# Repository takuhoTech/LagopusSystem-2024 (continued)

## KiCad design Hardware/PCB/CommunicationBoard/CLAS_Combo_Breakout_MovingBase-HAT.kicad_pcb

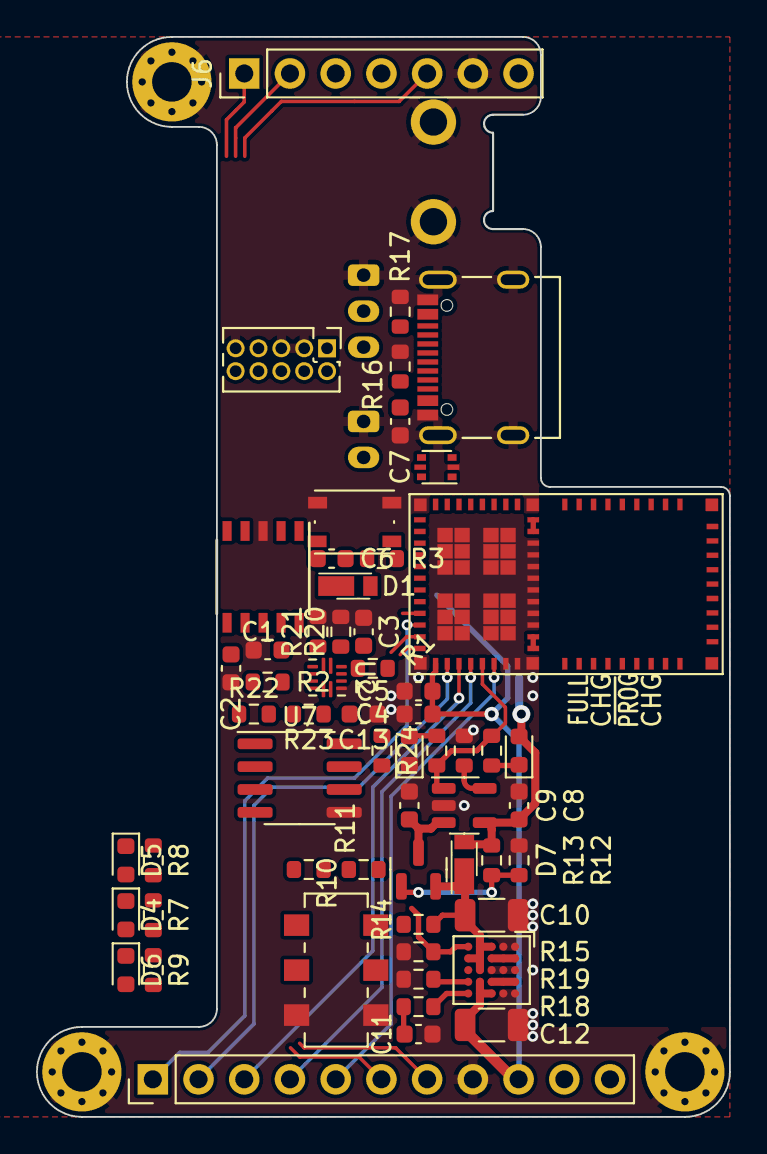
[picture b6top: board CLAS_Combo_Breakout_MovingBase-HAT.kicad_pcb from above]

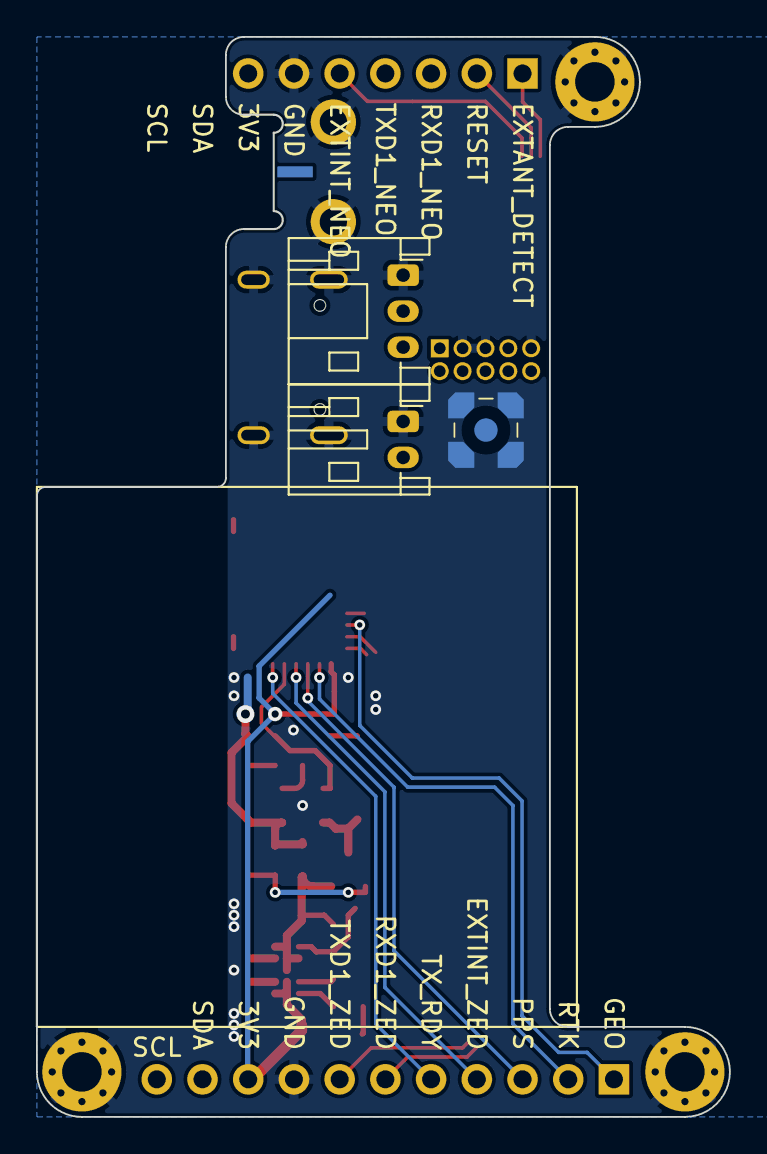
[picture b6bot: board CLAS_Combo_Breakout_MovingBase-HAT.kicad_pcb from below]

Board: 4 copper layers, 38.5 x 60.0 mm, 65 parts (4 on the bottom side), 57 nets.

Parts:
C1, C2, C3, C5, C6, C8, C13: 0.1u; C_0603_1608Metric
C4: 1u; C_0603_1608Metric
C7, C9: 47μF6.3V X5R 1608; C_0603_1608Metric
C10: 100μF10V X5R 3216; C_1206_3216Metric
C11: 2200pF50V CH 1608; C_0603_1608Metric
C12: 220μF4V X6S 3216; C_1206_3216Metric
D1, D7: CUHS20S30
D2: RED; LED_0603_1608Metric
D3: GREEN; LED_0603_1608Metric
D4: RTK; LED_0603_1608Metric
D5: GEO; LED_0603_1608Metric
D6: PPS; LED_0603_1608Metric
H1, H2, H3: MH; MountingHole_2.2mm_M2_Pad_Via
J1: MMCX; MMCX_Samtec_MMCX-P-P-H-ST-SM1_Male
J2: SMA; SMA_Molex_0732512440_embed
J3: SWD; PinHeader_2x05_P1.27mm_Vertical
J4: ZED; PinHeader_1x11_P2.54mm_Vertical
J5: BATT; JST_PH_S2B-PH-K_1x02_P2.00mm_Horizontal
J6: NEO; PinHeader_1x07_P2.54mm_Vertical
J7: USB_C_Receptacle_USB2.0; USB_C_Receptacle_5077CR-16-SMC2-BK-TR
J8: RS485; JST_PH_S3B-PH-K_1x03_P2.00mm_Horizontal
Q1: AO3415A; SOT-23
R1, R2: 33; R_0603_1608Metric
R3, R18, R20, R21, R22, R23: 10k; R_0603_1608Metric
R4: RILIM; R_0603_1608Metric
R5, R6, R7, R8, R9: 1k; R_0603_1608Metric
R10: 1M; R_0603_1608Metric
R11: 510k; R_0603_1608Metric
R12: 100k; R_0603_1608Metric
R13: 10; R_0603_1608Metric
R14: Rtop; R_0603_1608Metric
R15: Rbtm; R_0603_1608Metric
R16, R17: 5.1k; R_0603_1608Metric
R19: 26.2k; R_0603_1608Metric
R24: 120; R_0603_1608Metric
SW1: SW_Push; SW_Push_1P1T_NO_Vertical_Wuerth_434133025816
SW2: SW_SPDT; SW_SPDT_SSSS213202
U1: CH340K; SSOP-10_3.9x4.9mm_P1.00mm
U2: TMUX131; Texas_RMG0012A_1.8x1.8mm_P0.4mm
U3: ISP4520-AS; ISP4520-AS_with_Keep-Out
U4: MCP73831-2-OT; SOT-23-5
U5: LTM4693; Converter_DCDC_AnalogDevices_LTM4693
U6: USBLC6-2P6; SOT-666
U7: MAX3485; SOIC-8_3.9x4.9mm_P1.27mm

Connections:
+3.3V: C1.1, C2.1, C3.2, C4.1, C5.1, C12.1, C13.2, D1.1 (K), J3.1 (VTref), J4.9, J6.7, R3.1, R7.1, R22.1, R23.1, U1.7 (VCC), U1.10 (V3), U2.12 (VDD), U3.15 (VDD), U5.C5 (VOUT), U5.D4 (VOUT), U5.D5 (VOUT), U7.8 (VCC)
+BATT: C9.1, J5.2, Q1.3 (D), R10.1, U4.3 (VBAT)
/BaseMode: R21.1, U2.2 (SEL1), U3.9 (P0_13), U7.2 (~RE), U7.3 (DE)
/CH340K_RXD: U1.9 (RXD), U2.3 (S1B)
/CH340K_TXD: R2.2, U2.4 (S2B)
/D+: J7.A6 (D+), J7.B6 (D+), U1.1 (UD+), U6.1 (I/O1), U6.6 (I/O1)
/D-: J7.A7 (D-), J7.B7 (D-), U1.2 (UD-), U6.3 (I/O2), U6.4 (I/O2)
/DTR: C6.1, U1.4 (~DTR)
/EXTANT_DETECT: J6.1, U3.6 (P0_22)
/EXTINT_NEO: J6.5, U3.3 (P0_10/NFC2)
/EXTINT_ZED: J4.4, U3.18 (P0_30_AIN6)
/GEO: J4.1, R8.1, U3.11 (P0_05_AIN3)
/RESET: C6.2, D1.2 (A), J3.10 (~RESET), R3.2, SW1.1, U3.40 (P0_21/RESET)
/RESET_ZED_NEO: J6.2, U3.4 (P0_17)
/RS485_A: J8.3, R24.2, U7.6 (A)
/RS485_B: J8.2, R24.1, U7.7 (B)
/RS485_RXD: R23.2, U2.7 (S1A), U7.4 (DI)
/RS485_TXD: R22.2, U2.6 (S2C), U7.1 (RO)
/RTK: D4.1 (K), J4.2, U3.16 (P0_02_AIN0)
/RXD1_ZED: J4.6, U2.5 (S1C)
/RoverMode: R20.1, U2.1 (SEL0), U3.7 (P0_09/NFC1)
/SCL: J4.11, U3.5 (P0_07)
/SDA: J4.10, U3.2 (P0_12)
/SWDCLK: J3.4 (SWDCLK/TCK), U3.37 (SWDCLK)
/SWDIO: J3.2 (SWDIO/TMS), U3.38 (SWDIO)
/TP: J4.3, R9.1, U3.17 (P0_31_AIN7)
/TXD1_ZED: J4.7, U2.8 (S2A)
/TX_RDY: J4.5, U3.20 (P0_28_AIN4)
/VBAT: R10.2, R11.1, U3.13 (P0_03_AIN1)
/nRF52_RXD: U2.10 (D2), U3.8 (P0_08)
/nRF52_TXD: R1.1, U2.11 (D1)
/~CHG_STAT: R5.2, R6.1, U3.19 (P0_29_AIN5), U4.1 (STAT)
/~VBAT_EN: R11.2, U3.12 (P0_04_AIN2)
GND: C1.2, C2.2, C3.1, C4.2, C5.2, C7.1, C8.1, C9.2, C10.2, C11.2, C12.2, C13.1, D3.1 (K), D5.1 (K), D6.1 (K), H1.1, H2.1, H3.1, J1.2 (Ext), J2.2 (Ext), J3.3 (GND), J3.5 (GND), J3.9 (GNDDetect), J4.8, J5.1, J6.6, J7.A1 (GND), J7.A12 (GND), J7.B1 (GND), J7.B12 (GND), J7.S1 (SHIELD), J8.1, R4.1, R12.1, R15.2, R16.2, R17.2, R19.2, R20.2, R21.2, SW1.2, SW2.3 (C), U1.3 (GND), U2.9 (GND), U3.1 (GND), U3.14 (GND), U3.21 (GND), U3.22 (GND), U3.23 (GND), U3.26 (GND), U3.27 (GND), U3.28 (GND), U3.29 (GND), U3.30 (GND), U3.31 (GND), U3.32 (GND), U3.33 (GND), U3.36 (GND), U3.74 (GND), U4.2 (VSS), U5.A1 (GND), U5.A3 (GND), U5.A5 (GND), U5.B1 (GND), U5.B3 (GND), U5.B5 (GND), U5.C3 (GND), U6.2 (GND), U7.5 (GND)
unnamed: C11.1, R18.2
unnamed: D2.1 (K), R5.1
unnamed: D3.2 (A), R6.2
unnamed: D4.2 (A), R7.2
unnamed: D5.2 (A), R8.2
unnamed: D6.2 (A), R9.2
unnamed: J1.1 (In), J2.1 (In)
unnamed: J7.A5 (CC1), R16.1
unnamed: J7.B5 (CC2), R17.1
unnamed: Q1.1 (G), R12.2, R13.2
unnamed: R1.2, U3.10 (P0_06)
unnamed: R2.1, U1.8 (TXD)
unnamed: R4.2, U4.5 (PROG)
unnamed: R14.2, SW2.1 (A)
unnamed: R15.1, SW2.2 (B), U5.E1 (RUN/UVLO)
unnamed: R18.1, U5.E5 (COMP)
unnamed: R19.1, U5.E4 (FB)
unnamed: U3.24 (LORA_TR), U3.25 (LORA_ANT)
unnamed: U3.34 (BLE_ANT), U3.35 (BLE_TR)
unnamed: U5.A2 (SW1), U5.B2 (SW1), U5.C2 (SW1)
unnamed: U5.A4 (SW2), U5.B4 (SW2), U5.C4 (SW2)
VBUS: C7.2, C8.2, D2.2 (A), D7.2 (A), J7.A4 (VBUS), J7.A9 (VBUS), J7.B4 (VBUS), J7.B9 (VBUS), R13.1, U4.4 (VDD), U6.5 (VBUS)
VDD: C10.1, D7.1 (K), Q1.2 (S), R14.1, U5.C1 (VIN), U5.D1 (VIN), U5.D2 (VIN), U5.D3 (SS), U5.E2 (MODE/SYNC)

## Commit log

2023-11-18 add PCB project
2023-11-29 wiring
2023-12-11 バッテリモジュールを設計中
2023-12-14 電源回路配置
2023-12-21 Powerpathコンを使用、部品配置
2024-01-01 バッテリモジュール完成
2024-01-02 バッテリモジュールの部品表を生成
2024-01-02 部品表を編集
2024-01-02 部品表にサーミスタを追加
2024-01-03 ヒューズを追加、バッテリクリップの下のベタをBATTネットに
2024-01-03 クリアランスとシルク印刷を微調整
2024-01-10 保護回路付きの18500が入るように変更
2024-01-10 発注完了
2024-01-20 電源ボード製作完了、抵抗の値を反映
2024-01-20 抵抗の値をKiCadPCBに反映
2024-04-23 回路図確定
2024-04-23 回路図を微修正、基板を更新済み
2024-04-29 無線ボード配線7割
2024-04-30 残り未配線23
2024-04-30 未配線0
2024-04-30 VIA配置中
2024-05-02 書き込み用変換基板を作成、0.5/0.2mmビアを排除
2024-05-02 無線モジュールのビア置き終了、ひとまず完成
2024-05-07 Add MediaBoard
2024-05-10 WisdPi_Tiny_RP2040のシンボル/フットプリントを作成
2024-06-11 もろもろ更新
2024-06-12 汎用BLEライブラリ完成
2024-06-13 update BLE lib
2024-07-13 update BLE
2024-07-19 無線ボードのファーム、TWELITE以外完成
